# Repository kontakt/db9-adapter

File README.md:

# db9-adapter
An adapter for male and female DB9 connections

This adapter uses a standard DB9 male or female connector and two 5 position screw terminals to create a breakout for a serial or any other connection on a DB9. RS-232 signals are named for convenience, but that doesn't mean that's your only option.

Use the side marked 'M' for a male DB9, or the side marked 'F' for a female DB9.

# Parts
2x https://www.digikey.com/en/products/detail/w-rth-elektronik/691137710004/6644053

1x https://www.digikey.com/en/products/detail/amphenol-icc-fci/LD09S33E4GV00LF/4997294

OR

1x https://www.digikey.com/en/products/detail/amphenol-icc-fci/LD09P33E4GV00LF/4997288

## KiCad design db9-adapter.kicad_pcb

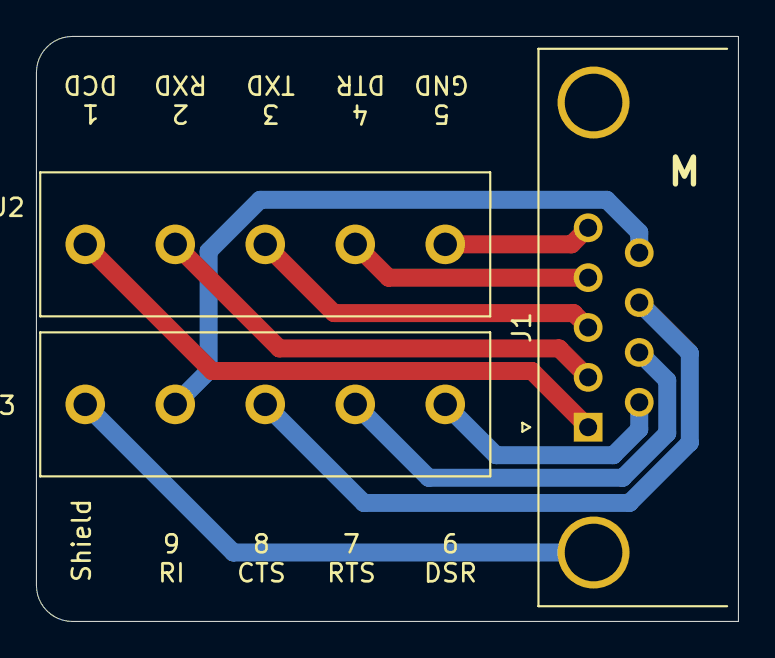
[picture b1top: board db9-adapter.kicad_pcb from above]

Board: 2 copper layers, 39.0 x 32.5 mm, 3 parts (0 on the bottom side), 10 nets.

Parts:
J1: DB9_Male_MountingHoles; DSUB-9_Male_Horizontal_P2.77x2.84mm_EdgePinOffset4.94mm_Hou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
J2, J3: Screw_Terminal_01x05; Wurth 5p

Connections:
unnamed: J1.0, J3.1
unnamed: J1.1, J2.1
unnamed: J1.2, J2.2
unnamed: J1.3, J2.3
unnamed: J1.4, J2.4
unnamed: J1.5, J2.5
unnamed: J1.6, J3.5
unnamed: J1.7, J3.4
unnamed: J1.8, J3.3
unnamed: J1.9, J3.2
